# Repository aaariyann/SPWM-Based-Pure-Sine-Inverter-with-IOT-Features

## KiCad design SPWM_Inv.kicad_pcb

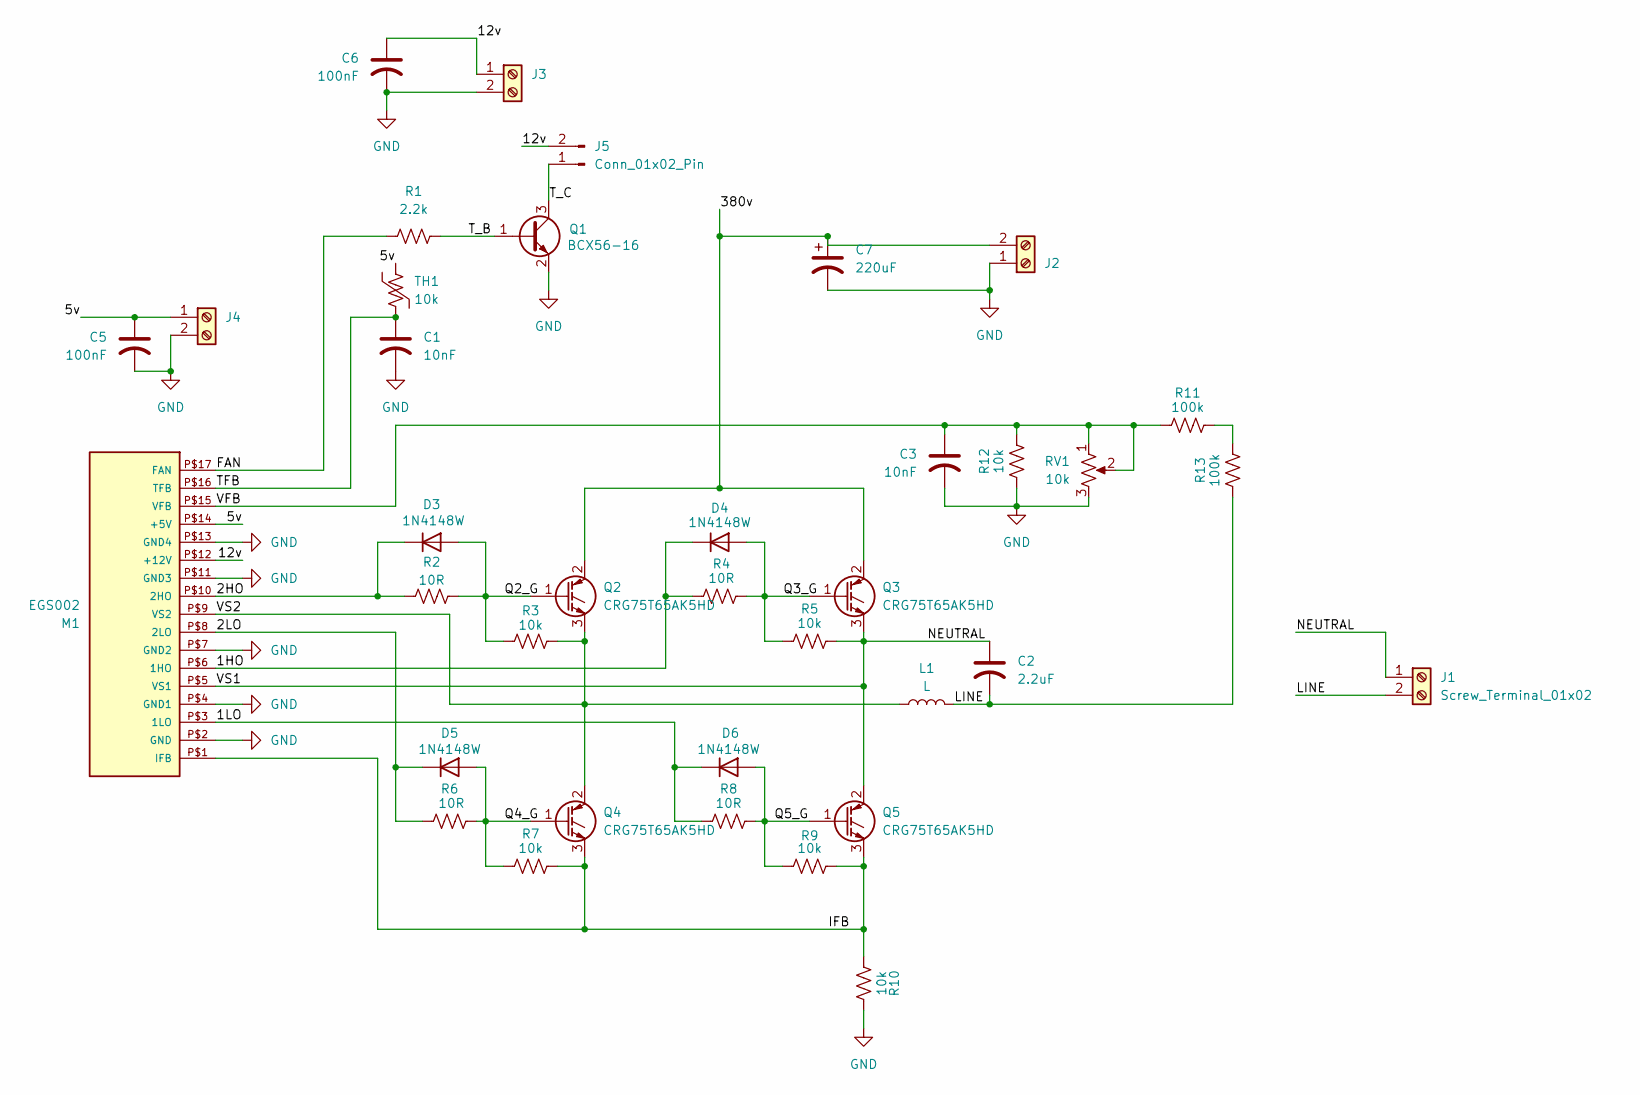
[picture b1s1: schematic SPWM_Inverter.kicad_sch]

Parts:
C1, C3: 10nF; C_1206_3216Metric_Pad1.33x1.80mm_HandSolder
C2: 2.2uF; C_Rect_L24.0mm_W7.0mm_P22.50mm_MKT
C5, C6: 100nF; C_1206_3216Metric_Pad1.33x1.80mm_HandSolder
C7: 220uF; CP_Radial_D30.0mm_P10.00mm_SnapIn
D3, D4, D5, D6: 1N4148W; D_SOD-123
J1, J2: Screw_Terminal_01x02; TerminalBlock_Ningbo-Kagnex_HB9500M_1x02_P9.5mm
J3, J4: Screw_Terminal_01x02; TerminalBlock_MaiXu_MX126-5.0-02P_1x02_P5.00mm
J5: Conn_01x02_Pin; JST_XH_B2B-XH-A_1x02_P2.50mm_Vertical
L1: L; L_Toroid_Vertical_L33.0mm_W17.8mm_P12.70mm_Pulse_KM-5
M1: EGS002
Q1: BCX56-16; SOT-89-3_Handsoldering
Q2, Q3, Q4, Q5: CRG75T65AK5HD; TO-247-3_Vertical
R1: 2.2k; R_1206_3216Metric_Pad1.30x1.75mm_HandSolder
R2, R4, R6, R8: 10R; R_1206_3216Metric_Pad1.30x1.75mm_HandSolder
R3, R5, R7, R9, R12: 10k; R_1206_3216Metric_Pad1.30x1.75mm_HandSolder
R10: 10k; R_2512_6332Metric_Pad1.40x3.35mm_HandSolder
R11, R13: 100k; R_1206_3216Metric_Pad1.30x1.75mm_HandSolder
RV1: 10k; Potentiometer_Bourns_3296W_Vertical
TH1: 10k; C_Disc_D3.0mm_W1.6mm_P2.50mm

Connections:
/Inversion Stage/1HO: D4.1 (K), M1.P$6 (1HO), R4.1
/Inversion Stage/1LO: D6.1 (K), M1.P$3 (1LO), R8.1
/Inversion Stage/2HO: D3.1 (K), M1.P$10 (2HO), R2.1
/Inversion Stage/2LO: D5.1 (K), M1.P$8 (2LO), R6.1
/Inversion Stage/5v: C5.1, J4.1, M1.P$14 (+5V), TH1.1
/Inversion Stage/12v: C6.1, J3.1, J5.2, M1.P$12 (+12V)
/Inversion Stage/380v: C7.1, J2.2, Q2.2 (C), Q3.2 (C)
/Inversion Stage/FAN: M1.P$17 (FAN), R1.1
/Inversion Stage/IFB: M1.P$1 (IFB), Q4.3 (E), Q5.3 (E), R7.2, R9.2, R10.1
/Inversion Stage/LINE: C2.2, J1.2, L1.2, R13.1
/Inversion Stage/NEUTRAL: C2.1, J1.1, M1.P$5 (VS1), Q3.3 (E), Q5.2 (C), R5.2
/Inversion Stage/Q2_G: D3.2 (A), Q2.1 (G), R2.2, R3.1
/Inversion Stage/Q3_G: D4.2 (A), Q3.1 (G), R4.2, R5.1
/Inversion Stage/Q4_G: D5.2 (A), Q4.1 (G), R6.2, R7.1
/Inversion Stage/Q5_G: D6.2 (A), Q5.1 (G), R8.2, R9.1
/Inversion Stage/TFB: C1.1, M1.P$16 (TFB), TH1.2
/Inversion Stage/T_B: Q1.1 (B), R1.2
/Inversion Stage/T_C: J5.1, Q1.3 (C)
/Inversion Stage/VFB: C3.1, M1.P$15 (VFB), R11.1, R12.2, RV1.1, RV1.2
/Inversion Stage/VS2: L1.1, M1.P$9 (VS2), Q2.3 (E), Q4.2 (C), R3.2
GND: C1.2, C3.2, C5.2, C6.2, C7.2, J2.1, J3.2, J4.2, M1.P$2 (GND), M1.P$4 (GND1), M1.P$7 (GND2), M1.P$11 (GND3), M1.P$13 (GND4), Q1.2 (E), R10.2, R12.1, RV1.3
unnamed: R11.2, R13.2

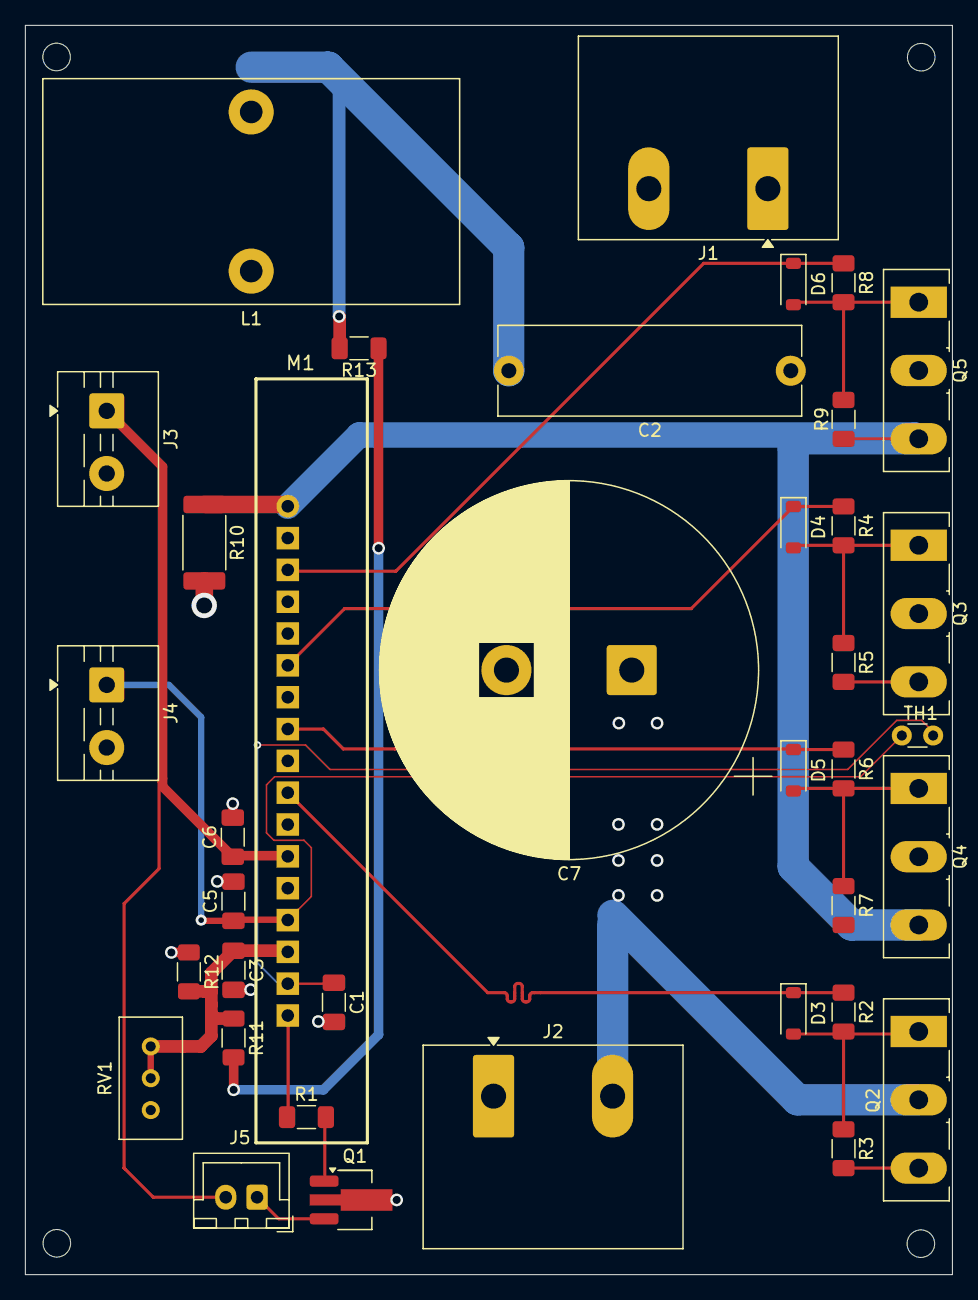
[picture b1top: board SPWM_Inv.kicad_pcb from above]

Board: 4 copper layers, 74.0 x 99.7 mm, 37 parts (0 on the bottom side), 22 nets.

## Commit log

2026-05-21 Init
2026-05-23 Footprint finalization
2026-05-28 Layout Update
2026-05-31 Layout Finalized
2026-06-01 Routing Finished
2026-06-03 Version1_InverterStage
